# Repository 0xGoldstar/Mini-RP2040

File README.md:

# Mini-RP2040
This is a simple controller based on RP2040 MCU and has one data output. Great for controlling ws2811, ws2812, or similar strips. This project was created using **KiCad 7.0**

## PCB Design

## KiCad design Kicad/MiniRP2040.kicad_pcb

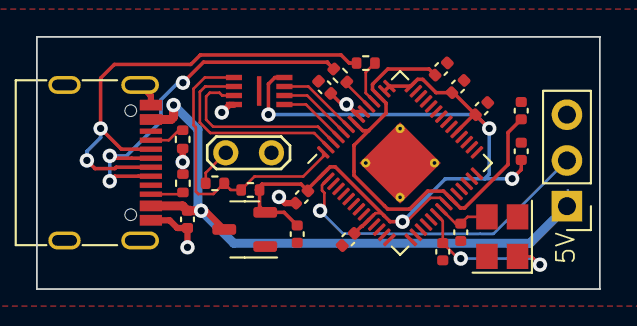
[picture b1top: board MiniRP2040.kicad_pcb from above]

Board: 2 copper layers, 31.3 x 14.0 mm, 25 parts (0 on the bottom side), 20 nets.

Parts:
C1, C2: 1uF; C_0402_1005Metric
C4, C5, C7, C8, C11, C12, C14: 100n; C_0402_1005Metric
C15, C16: 27p; C_0402_1005Metric
C17: 10u; C_0402_1005Metric
IC1: W25Q16JVUXIQ; SON50P300X200X60-9N
J1: USB_C_Receptacle_USB2.0; USB_C_Receptacle_G-Switch_GT-USB-7010ASV
J2: Conn_01x02_Socket; TestPoint_2Pads_Pitch2.54mm_Drill0.8mm
J3: Conn_01x03_Socket; PinHeader_1x03_P2.54mm_Vertical
R1, R2: 27.4; R_0402_1005Metric
R3: DNF; R_0402_1005Metric
R4: 1k; R_0402_1005Metric
R6, R7: 5.1k; R_0402_1005Metric
U1: XC6206PxxxMR; SOT-23-3
U2: RP2040; QFN-56-1EP_7x7mm_P0.4mm_EP3.2x3.2mm_ThermalVias
Y2: Crystal_GND23_Small; Crystal_SMD_3225-4Pin_3.2x2.5mm

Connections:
+1V1: C4.1, C5.1, U2.23 (DVDD), U2.45 (VREG_VOUT), U2.50 (DVDD)
+3.3V: C2.1, C7.1, C8.1, C11.1, C12.1, C14.1, C17.1, IC1.8 (VCC), R3.1, U1.2 (VO), U2.1 (IOVDD), U2.10 (IOVDD), U2.22 (IOVDD), U2.33 (IOVDD), U2.42 (IOVDD), U2.43 (ADC_AVDD), U2.44 (VREG_IN), U2.48 (USB_VDD), U2.49 (IOVDD)
+5V: C1.1, J1.A4 (VBUS), J1.A9 (VBUS), J1.B4 (VBUS), J1.B9 (VBUS), J3.1, U1.3 (VI)
/CLK: IC1.6 (CLK), U2.52 (QSPI_SCLK)
/D0: IC1.5 (DI_(IO0)), U2.53 (QSPI_SD0)
/D1: IC1.2 (DO_(IO1)), U2.55 (QSPI_SD1)
/D2: IC1.3 (~WP_(IO2)), U2.54 (QSPI_SD2)
/D3: IC1.7 (~HOLD_OR_RESET_(IO3)), U2.51 (QSPI_SD3)
/D+: J1.A6 (D+), J1.B6 (D+), R1.1
/D-: J1.A7 (D-), J1.B7 (D-), R2.1
/SS: IC1.1 (~CS), R3.2, R4.2, U2.56 (QSPI_SS)
/XIN: C16.2, U2.20 (XIN), Y2.1
/XOUT: C15.2, U2.21 (XOUT), Y2.3
GND: C1.2, C2.2, C4.2, C5.2, C7.2, C8.2, C11.2, C12.2, C14.2, C15.1, C16.1, C17.2, IC1.4 (GND), J1.A1 (GND), J1.A12 (GND), J1.B1 (GND), J1.B12 (GND), J1.S1 (SHIELD), J2.1, J3.3, R6.1, R7.1, U1.1 (GND), U2.57 (GND), Y2.2, Y2.4
unnamed: J1.A5 (CC1), R7.2
unnamed: J1.B5 (CC2), R6.2
unnamed: J2.2, R4.1
unnamed: J3.2, U2.2 (GPIO0)
unnamed: R2.2, U2.46 (USB_DM)
unnamed: R1.2, U2.47 (USB_DP)

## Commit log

2025-06-05 Add .gitignore for KiCad cache files
2025-06-05 Update README and added PCB image
2025-06-05 Add CC BY-NC 4.0 license
2025-06-05 cleaned up files
